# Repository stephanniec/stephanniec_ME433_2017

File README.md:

### ME 433: Advanced Mechatronics Course Projects
March 2017 - June 2017

## About
This repository contains scripts for various mechatronics projects completed for the ME 433 course at Northwestern.

## Contents
#### HW1: Breadboard Prototyping<br>
* pic32mx250f128b microcontroller breadboard circuit diagram and picture<br>
* Circuit validation code which toggles an LED on and off

#### HW2: PCB Design Part I<br>
* Custom pic32mx250f128b Eagle library
* pic32mx250f128b PCB schematic

#### HW3: PCB Design Part II<br>

* PCB .brd Eagle file
* Compressed PCB Gerber files

#### HW4: SPI Device Communication<br>
* SPI communication with an MCP4902 DAC chip
* Code tells the DAC to output a 10Hz sine wave and 5Hz triangle wave

#### HW5: I2C Device Communication<br>
* I2C communication with an MCP23008 chip
* Code tells the chip to turn off a yellow LED when a button hooked up to GP7 is pressed

#### HW6: LCD Display<br>

* TFT LCD display using SPI communication
* Code prints the image of a hedgehog and "Hello World!" to the screen, draws a progress bar which fills as a counter increases from 0-100, and outputs a live reading of the frames per second rate

#### HW7: Accelerometer Display<br>

* LCD progress bar display of accelerometer xy readings from an LSM6DS33 chip

#### HW8: Working with Harmony<br>
* Replica of HW7 using Harmony

#### HW9: USB Device Communication<br>
* Accelerometer data display using PIC-USB communication

#### HW10: Digital Signal Processing<br>
* Digital signal processing of IMU readouts
* Compared the performance of 3 different low pass filters: MAF, IIR, and FIR

#### HW11: USB Mouse Prototype<br>
* IMU mouse prototype
* Controls the trajectory of a cursor via PIC-USB communication

#### HW12: Android Programing<br>

* Basic slider bar Android application written in JAVA

#### HW13: Android Color Recognition<br>
* Color identification Android application written in JAVA

#### HW14: USB Communication with an Android Phone<br>

* Android phone and PIC microcontroller communication
* Phone sends the position of a slider bar to the chip
* Chip continuously streams increasing integer values
* When an input from the phone is received, the PIC will return the slider position as it outputs numbers

#### HW15: CAD<br>

* CAD designs of a wheel and a box with a living hinge built in OnShape

#### HW16: 3D Printing<br>

* Assembled 3D printed wheel prototypes

#### HW17: Laser Cutting<br>

* Assembled living hinge box

#### HW18: Motor Control Application<br>
* Created a JAVA android application which can individually set the speed and direction of two DC motors
* PWM output is determined by the position of two slider bars
* Wheel direction is determined by the position of two switches

#### HW19: Path Center Identification<br>
* Android application uses the rear camera scan the environment
* The resulting Bitmap read is analyzed for areas where green meets red
* A horizontal line is drawn where the android believes the path starts and ends
* The center of mass of the line is denoted by a red dot

#### HW20: Line-following Robot

* Consolidated motor control and path detection code
* Constructed a small vehicle to house the motors and circuitry
* Implemented proportional control to moderate the speed of the wheels
* Filtered the center of mass positions so only the average points of the Bitmap's last 120 rows are analyzed
* Applied a threshold pixel range which halts one wheel of the robot if the COM point is lost

Note: Servo motor code was commented out to let the car run at max speed without needing to divert power elsewhere

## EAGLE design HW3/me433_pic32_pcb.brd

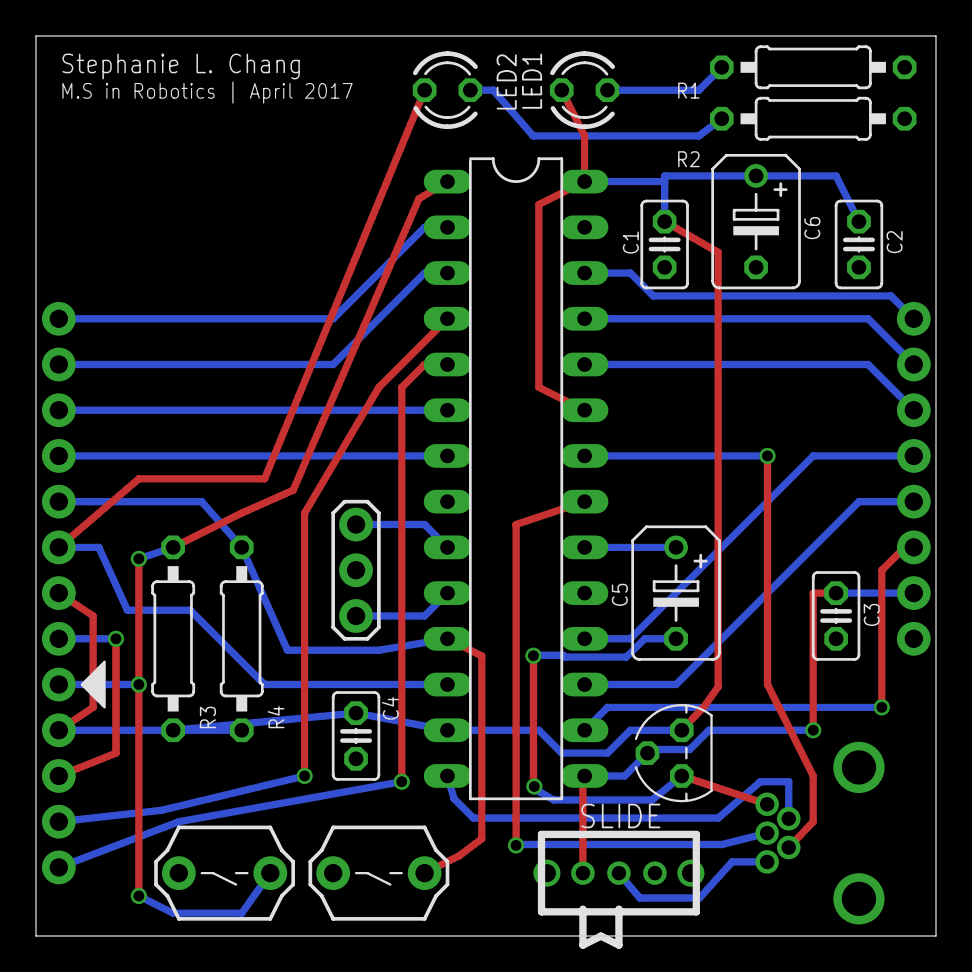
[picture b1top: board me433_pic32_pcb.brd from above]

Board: 2 copper layers, 50.0 x 50.0 mm, 22 parts (0 on the bottom side), 27 nets.

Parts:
C1, C2, C3, C4: 0.1uF; C025-025X050
C5, C6: 10uF; B45181B
J1: USB-MB-H
LED1: Red; LED3MM
LED2: Green; LED3MM
R1, R2: 330; 0207/10
R3, R4: 10k; 0207/10
U1: PIC32MX250F128B; DIL28-3
U2: SLIDE
U3: MCP1702; TO92
U4: RESET; PB
U5: USER; PB
U6, U7: CONN_08; 1X08
U8: PICKIT3; 1X05
U9: 8MHz; OSC

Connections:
+3V3: C1.1, C2.1, C4.1, C6.+, LED1.A, R3.2, R4.2, U1.13, U1.23, U1.28, U3.3, U7.2, U8.2
+5V: C3.1, U1.15, U2.3, U3.2, U6.2
A0: U1.2, U7.8
A1: U1.3, U7.7
A4/LED: LED2.A, U1.12, U7.3
B2: U1.6, U7.6
B3: U1.7, U7.5
B4/USER: R4.1, U1.11, U5.1, U7.4
B7: U1.16, U6.3
B8: U1.17, U6.4
B9: U1.18, U6.5
B13: U1.24, U6.6
B14: U1.25, U6.7
B15: U1.26, U6.8
D+: J1.D+, U1.21
D-: J1.D-, U1.22
GND: C1.2, C2.2, C3.2, C4.2, C5.-, C6.-, J1.GND, R1.1, R2.1, U1.8, U1.19, U1.27, U3.1, U4.2, U5.2, U6.1, U7.1, U8.3, U9.2
MCLR: R3.1, U1.1, U4.1, U8.1
unnamed: LED2.K, R2.2
unnamed: LED1.K, R1.2
unnamed: U1.9, U9.1
unnamed: U1.10, U9.3
unnamed: C5.+, U1.20
PGC: U1.5, U8.5
PGD: U1.4, U8.4
USBID: J1.ID, U1.14
VBUS: J1.VBUS, U2.2

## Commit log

2017-03-29 First commit. Added noisy and clean 3.3V imgs. Started new project.
2017-03-29 Blank main.c
2017-03-29 main.c first test
2017-03-29 Code done. Added photo of pic32 circuit
2017-03-29 Added photo of pic32 circuit
2017-03-29 Code done. Pin 11 push button now turns off LED when held down
2017-03-29 Clean final code. Deleted weird add-ins conflict inserted
2017-03-29 Final final code. Deleted overlooked, duplicate LATAINV inserted from conflict
2017-03-30 HW1 finished. Added circuit diagram sketch. Updated README.
2017-04-04 pic32 pcb library and schematic
2017-04-04 Updated README.md with HW2
2017-04-07 Eagle .brd file and gerber files for pic32 pcb
2017-04-07 Updated README and added board image
2017-04-07 Fixed image path
2017-04-07 Fixed alignment
2017-04-17 Restarting SPI. Something went weird with old dir.
2017-04-17 Removed unecessary CS lines.
2017-04-17 Waveforms showing
2017-04-17 Adjusted SPI sine and ramp wave frequencies to 10Hz and 5Hz
2017-04-17 SPI circuit diagram
2017-04-30 Starting hw5
2017-05-01 header file and functions created. checkpoint.
2017-05-01 Hw5 done. Circuit works.
2017-05-01 Starting hw6
2017-05-01 Editing hw5 annotations
2017-05-01 Character test successful.
2017-05-01 Hedgehog!
2017-05-04 Hw6 done
2017-05-10 Starting hw7 IMU accelerometer
2017-05-11 accel data correctly read and scaled
2017-05-12 x bar working
2017-05-12 hw7 done
2017-05-12 Hw7 done.
2017-05-12 HW8 done. Bare bones min files for running IMU
2017-05-12 Weird loading error fixed?
2017-05-12 Starting hw9
2017-05-13 Hw9 working
2017-05-16 HW12 done. HW9 USB connection issues not fixed.
2017-05-16 App picture
2017-05-16 Resize
2017-05-16 HW13 done. FPS is very low.
2017-05-18 HW15 flower wheel CAD file done
2017-05-20 Camera feed enabled with OpenCV
2017-05-20 Demo color identifier with OpenCV worksgit add --all!
2017-05-25 Wheel 2
2017-05-25 HW16 done
2017-05-26 HW9 USB comm finally works!
2017-05-26 Starting HW11 USB Mouse
2017-05-27 HW11 done. USB miracle moment finally happened.
2017-05-27 Scaling IMU values for good video
2017-05-28 Almost there. Weird FIR offset
2017-05-28 HW10 done.
2017-05-28 HW10 filter observations
2017-05-28 Getting notes to display
2017-05-28 Fixing readme
2017-05-28 Added more imgs to README
2017-05-29 HW15 done. Box pictures added
2017-05-29 Starting HW14
2017-05-29 HW14 done
2017-05-29 README section clarification
2017-06-02 HW17 done
2017-06-03 Starting HW18
2017-06-03 pcb setup works with HW14 code
2017-06-03 HW18 restart
2017-06-03 Clean hw 14 copy
2017-06-03 HW18 has a clean copy of HW14 android code
2017-06-04 Can set motor speed using Android app.
2017-06-04 Can set direction of motors. Can modulate speed and direction separately for each wheel. HW18 done
2017-06-05 Starting HW19. Duplicating HW13 first.
2017-06-05 HW19 done. Need to tune parameters
2017-06-08 Starting final project. Clean motor control replica
2017-06-08 Rudimentary line following. Not tested
2017-06-09 Line following works!
2017-06-10 Final README update
